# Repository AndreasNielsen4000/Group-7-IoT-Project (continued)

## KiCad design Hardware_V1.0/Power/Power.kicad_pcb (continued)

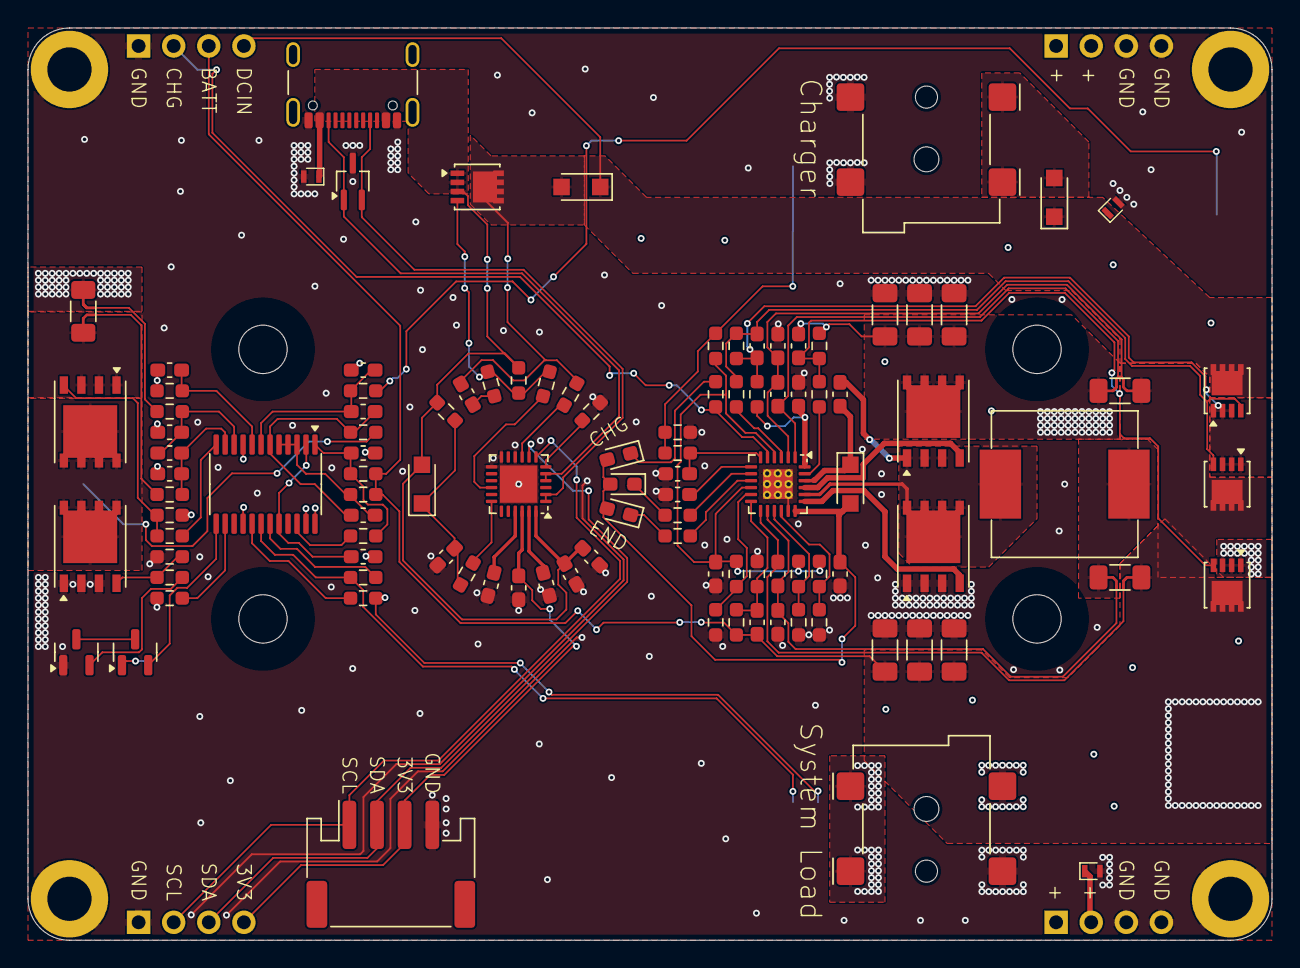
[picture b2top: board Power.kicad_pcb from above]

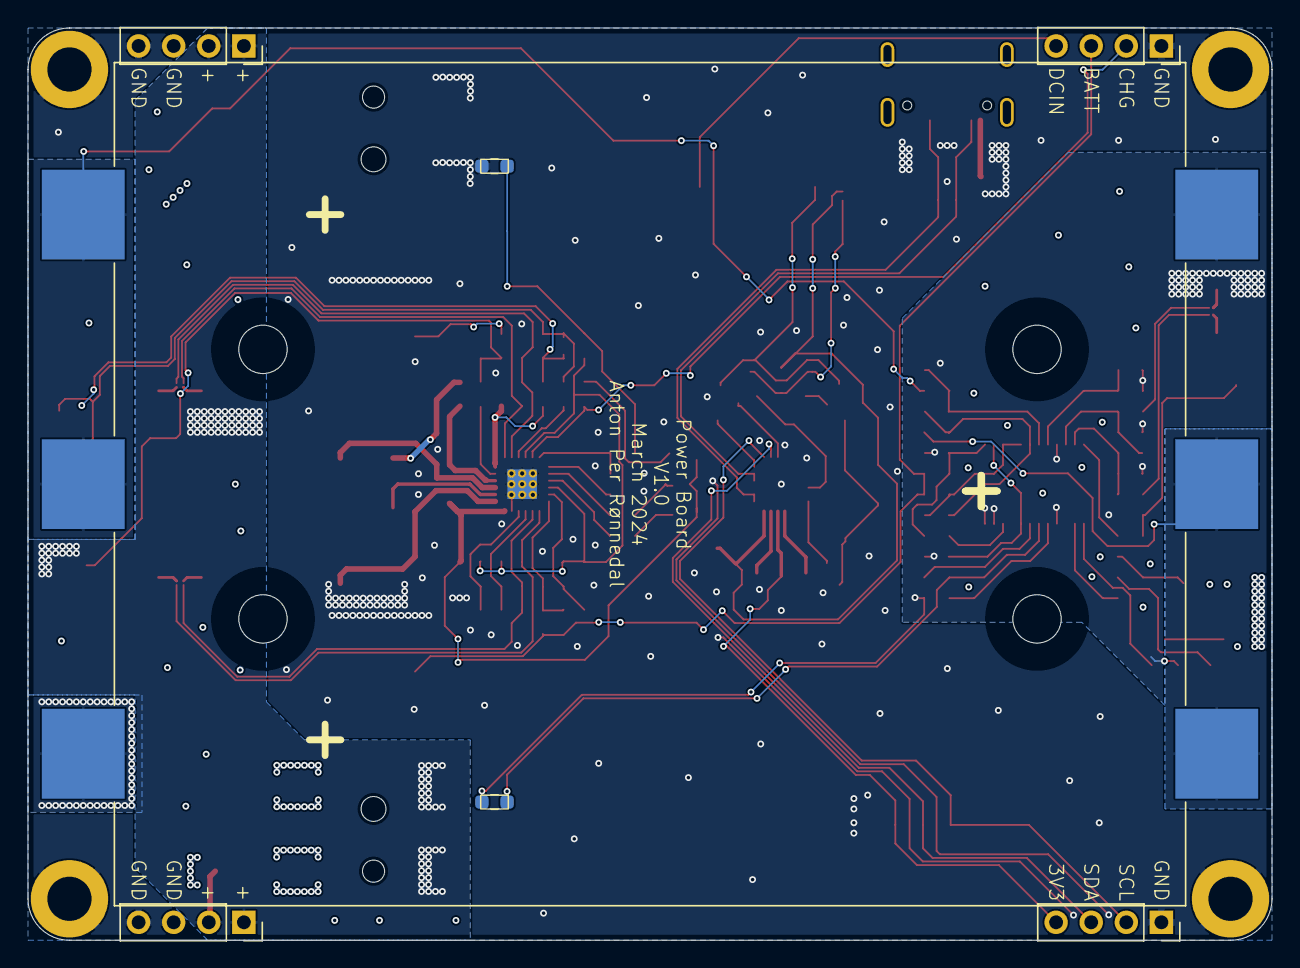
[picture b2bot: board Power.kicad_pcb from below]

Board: 4 copper layers, 90.0 x 66.0 mm, 119 parts (11 on the bottom side), 78 nets.

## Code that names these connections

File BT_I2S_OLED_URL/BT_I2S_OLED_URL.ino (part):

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
//LED & BUTTON PINS
#define PIN_LED 0
#define PIN_BTN 35
#define PIN_ENC_A 27
#define PIN_ENC_B 14
#define PIN_LED_R 32
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
//AMP & PSU PINS
#define PIN_AMP_EN 2
#define PIN_PSU_EN 33
#define PD_MUTE 12

//Power Delivery I2C Address & Frequency
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#define BTN_LONG_PRESS 100

//Battery & Charging
#define PIN_BATT 39
#define PIN_CHG 36

//Timer objects
ESP32Timer Timer0(0); //4 timers are available (from 0 to 3)
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//Timer 3 ISR used for handling the power button and changing the device mode, contains the state machine for the device
bool IRAM_ATTR Timer3_ISR(void * timerNo){
    /*Power logic*/ 
    bool BTN_IN = analogRead(PIN_BTN) >= SW_THRESHOLD;
    if (BTN_IN) {
        holdCounter_++;
    }
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        } else if (!BTN_IN && holdCounter_ > 1 && holdCounter_ < BTN_SINGLE_PRESS) {
            //Save current mode in the third bit of MOD_IN_
            DeviceMode temp = deviceMode_;
            if (digitalRead(PIN_CHG)) {
                temp = NONE;
            } else {
                temp = CHG;
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        } else if (!BTN_IN && holdCounter_ > 1 && holdCounter_ < BTN_SINGLE_PRESS) {
            //Save current mode in the third bit of MOD_IN_
            DeviceMode temp = deviceMode_;
            if (digitalRead(PIN_CHG)) {
                temp = NONE;
            } else {
                temp = CHG;
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        if (holdCounter_ > BTN_SINGLE_PRESS) {
          holdCounter_ = 0;
        }
        if (digitalRead(PIN_CHG)) {
            digitalWrite(PIN_PSU_EN,HIGH);
            deviceMode_ = NONE;
            MOD_IN_ = (deviceMode_ & 0x07); 
            holdCounter_ = 0;
            deviceModeChanged_ = true;
        }
        digitalWrite(PIN_PSU_EN,HIGH);
        break;
    case NONE:
        if (holdCounter_ > BTN_LONG_PRESS && BTN_IN) {
          digitalWrite(PIN_PSU_EN,LOW);
        } else {
        digitalWrite(PIN_PSU_EN,HIGH);
        }
        if (!BTN_IN && holdCounter_ > 1 && holdCounter_ < BTN_SINGLE_PRESS) {
            deviceMode_ = static_cast<t_DeviceMode>((MOD_IN_ >> 2) & 0x03);
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        if (!BTN_IN && holdCounter_ < BTN_LONG_PRESS) {
          holdCounter_ = 0;
        }
        if (!digitalRead(PIN_CHG)) {
            deviceMode_ = CHG;
            MOD_IN_ = (deviceMode_ & 0x07); 
            holdCounter_ = 0;
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
void setup() {
    //Set and enable PSU latch
    pinMode(PIN_PSU_EN,OUTPUT);
    digitalWrite(PIN_PSU_EN,HIGH);

    pinMode(PIN_BTN,INPUT); //Encoder button
    pinMode(PIN_BATT,INPUT); //Battery level
    pinMode(PD_MUTE,OUTPUT); //Mute pin
    pinMode(PIN_CHG,INPUT); //Charging status

    pinMode(PIN_LED, OUTPUT); // Onboard LED

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* Process the battery level and convert it to a percentage
*/
void processBatteryLevel(void){
  float voltage = analogRead(PIN_BATT)*3.3/4096*6;  // Reading an calculating voltage level
  int8_t percent = (voltage/12.4)*100;              // Converting to percent
  batteryLevel_ = percent;
}
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
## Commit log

2024-03-21 New readme added
2024-04-04 Added first draft of A2DP and WiF compatible code
2024-04-07 Progress on OLED and other things
2024-04-10 OLED improvements, improved behavior. Added serial control and bluetooth volume feedback. Added MARK comments for visibility in VSCode.
2024-04-11 Minor OLED improvements
2024-04-11 Blink
2024-04-11 Added ESP32 to azure code
    based on example given by
    https://github.com/microsoft/azure-iot-central-esp32-sample
2024-04-11 Integration started, added states
2024-04-12 V1.0
2024-04-17 Ported encoder functionality, added volume control, started button control
2024-04-18 More integration progress
2024-04-19 ESP32 HTTP GET code
    return url oldURLString and name oldNameString as strings
2024-04-23 1. try to add the http get to the code
2024-04-24 Added post function wit h voltageread and process
2024-04-24 Many improvements, WiFi AMP stable
2024-04-24 Working "state machine" prototype
2024-04-24 First implementation of State and Charge light
2024-04-24 Updated Charge LEDs
2024-04-24 Working http test code run
2024-04-24 Minor fixes
2024-04-24 Minor fixes 2.0
2024-04-24 Minor fixes 3.0 - WiFi stream is broken
2024-04-25 Add battery http post
2024-04-25 New state machine
2024-04-25 PIN definitions for NRF
2024-04-25 Added battery on display, testing PSU latching
2024-04-25 IoT HUB for azure server
2024-04-25 nRF for Speaker
    My best guess at what would be suitable for nrf for the Speaker, it transmitts all info in one char array at smaller than 27 bites
2024-04-26 Progress on NRF Integration
2024-04-27 Added nRF network functionality, IoT integration working
2024-04-27 Minor clean-up, added volume-dependent pause/play in BT
2024-04-27 Clean up and comments, minor improvements
2024-04-27 Added markdown for flowcharts
2024-04-28 chart/diagram updates
2024-04-28 3D Model
    this file contains the link to download the 3D model created with fusion 360 and can be downloaded in any format
2024-04-30 IoT is working
2024-05-01 Minor improvements and updated flowchart
2024-05-04 Updated for presentation
2024-05-04 Added description and credits
2024-05-04 Minor clean up
2024-05-05 Added demo video
2024-05-05 Added communication flow and updated readme
2024-05-05 Update README.md
    Embedded videos
2024-05-05 Added gif of communication overview
2024-05-05 Updated ComFlow.gif to one without black screen
2024-05-05 New ComFlow.gif without black screen
2024-05-05 Clean up of repository
2024-05-06 remove last test folders
